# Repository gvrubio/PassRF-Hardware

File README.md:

How frustrating is it to type a password on a computer where you haven't set up your favorite password manager? Quite annoying, isn't it?

## Well, allow me to introduce ✨PassRF✨

PassRF serves as a bridge between your smartphone's password manager and the target computer.

It functions by creating an access point with a small HTTP server. This server includes a field where you can paste the password you want PassRF to input.

It will act as an USB keyboard, no drivers required, nothing to install on the destination device.

## The current features of PassRF include:

- WPA2-PSK AES
- An easy-to-use first-run wizard.
- Automatic random password generation upon initial setup. You get a 32-character password with symbols, numbers, and more.
- Only one client is allowed to be connected to the access point, ensuring the sent password can't be intercepted.

## Here are the steps to get it up and running:

1. Assemble the hardware:<br>
2. Flash the devices. Your should use "Arduino Leonardo" for the arduino, and "Wemos D1 Mini" for the ESP8266.
3. Connect to the "SETUP" access point.
4. Go to 192.168.4.1 in your browser.
5. Copy the WPA password.
6. Click "SAVE PASSWORD!"
7. A new network named AP-XXXXXX (<- Randomly Generated Name) should become visible. This is still WIP.
8. Connect to it using the password you copied earlier.
9. Access 192.168.4.1 in your browser again. Now, you should see the password input field.

## What's the hardware needed?
The hardware is dirt cheap and should be easy to buy and build.

- A Wemos D1 Mini ESP8266, around 3 or 4€.
- An arduino pro micro, also around 3 or 4€.
- A TXE108E 3.3v to 5v bidirectional voltage level converter, you would not believe it, it's around 3 or 4€ as well!!!! 😲.
- Soldering skills, wire. You could even use some of those arduino bridge wires, and no soldering is required.
- I have an initial design for a PCB, it is my first time working with Kicad, so expect some bullshit from it, you are free to take it and modify it.

Here is how the PCB looks:

## What are some features expected on the future:
- ~~Reset button to restart the WPA password wizard.~~

    - Put a 10k resistor between D1 and GND, then short D1 and 3.3v for 5 seconds until the led turns off. SETUP will show up again to reset your WPA password.

- Automatic password reset on different client connection.
- Client whitelist.
- Android Keepass2Android integration plugin.
- Serial CRC32 checksum and json data over serial.
- Better Web UI, now it just works 😅

## Which things could make it even more secure:

- SSL between the smartphone and the web server. <- This hasn't been implemented because it would significantly complicate the setup process. I'm open to hearing other ideas.
- Metalic case to avoid the serial signal to be catched over the air. Help us Faraday. <- Use some altoids or any other metallic case, solder a wire to the case and put it to the device ground.
- Encryption on the serial communication. <- AES on an 8-bit arduino? Maybe xD. I hear ideas as well.

## The rest of the repos:
  Link to the hardware:
  [LINK](https://github.com/gvrubio/PassRF-Hardware)

  Link to the Arduino code:
  [LINK](https://github.com/gvrubio/PassRF-Arduino)

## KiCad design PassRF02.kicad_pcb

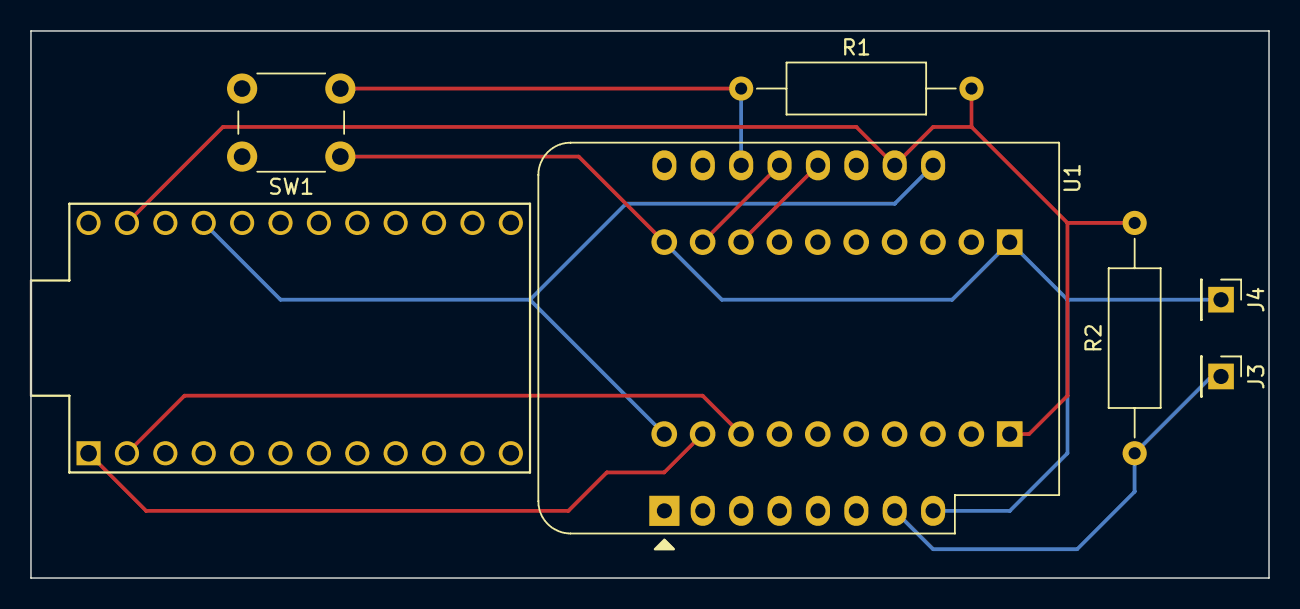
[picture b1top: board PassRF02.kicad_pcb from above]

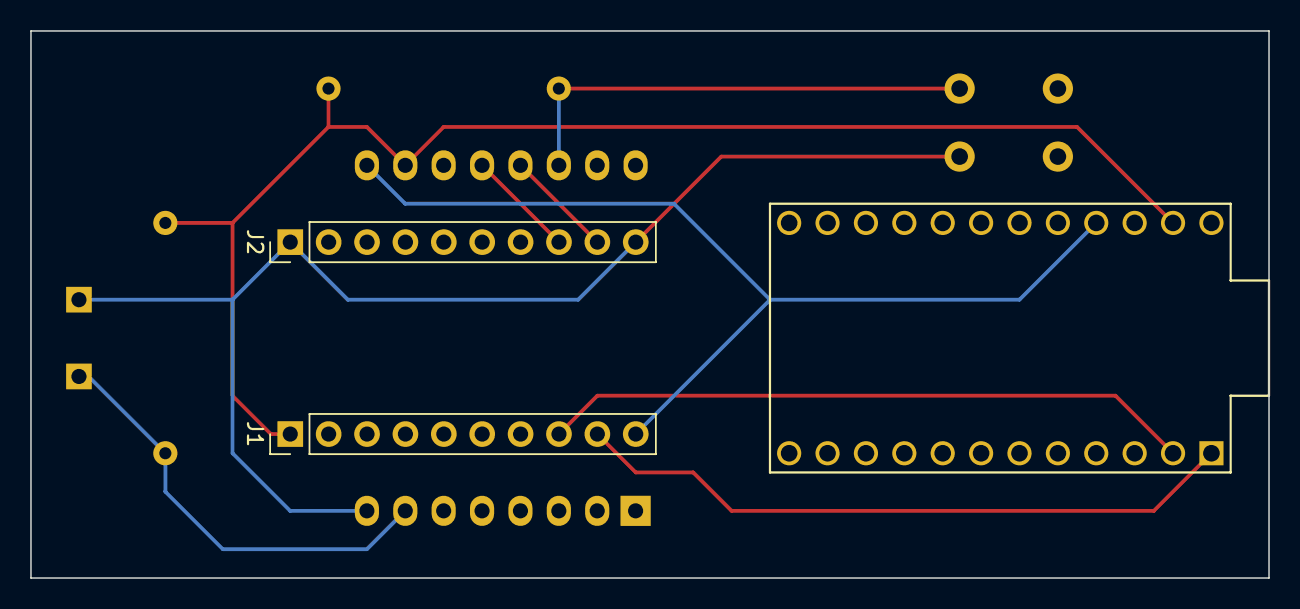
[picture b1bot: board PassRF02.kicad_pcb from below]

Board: 2 copper layers, 81.9 x 36.2 mm, 9 parts (2 on the bottom side), 9 nets.

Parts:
J1, J2: PINHD_1x10_Male; PinHeader_1x10_P2.54mm_Vertical
J3, J4: PINHD_1x1_Male; PinHeader_1x01_P2.54mm_Vertical
R1, R2: Resistor_0.5W; R_Axial_DIN0309_L9.0mm_D3.2mm_P15.24mm_Horizontal
SW1: Push_Button; SW_PUSH_6mm
U1: WeMos_D1_mini; WEMOS_D1_mini_light
U2: ProMicro

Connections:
unnamed: J2.1, J2.10, J4.1, SW1.1, U1.8 (3V3)
unnamed: J1.10, U1.9 (5V), U2.21 (VCC)
unnamed: J3.1, R2.1, U1.7 (CS/D8)
unnamed: J2.8, U1.12 (D3)
unnamed: J1.1, R1.2, R2.2, U1.10 (GND), U2.23 (GND)
unnamed: R1.1, SW1.2, U1.14 (SCL/D1)
unnamed: J2.9, U1.13 (SDA/D2)
unnamed: J1.8, U2.2 (RX)
unnamed: J1.9, U2.1 (TX)

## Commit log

2023-10-27 Add Links
2023-10-28 Add reset procedure to README
2023-11-03 Add reset button and killswitch
